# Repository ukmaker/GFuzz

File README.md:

# GFuzz
Guitar fuzz pedal with old-school fuzz-face and modern circuitry using germanium diodes

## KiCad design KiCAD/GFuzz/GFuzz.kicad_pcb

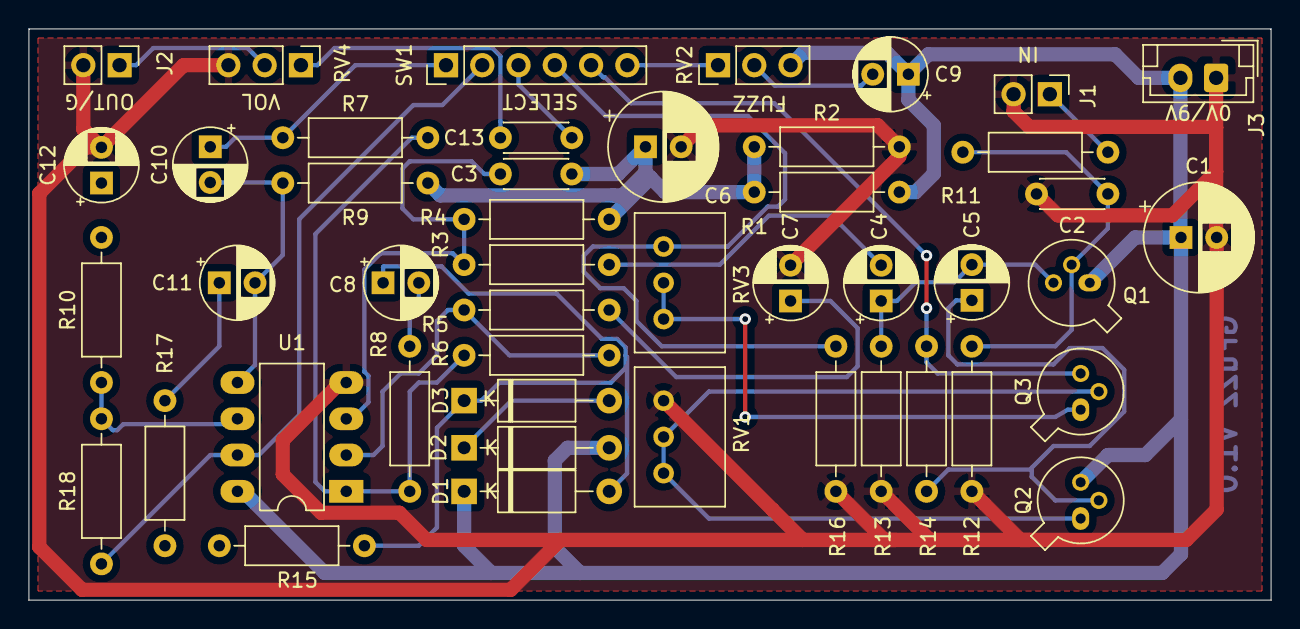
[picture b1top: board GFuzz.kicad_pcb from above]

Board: 2 copper layers, 87.0 x 40.0 mm, 46 parts (0 on the bottom side), 31 nets.

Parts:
C1, C6: 100u; CP_Radial_D7.5mm_P2.50mm
C2, C3: 1n; C_Disc_D4.3mm_W1.9mm_P5.00mm
C4, C5: 2u2; CP_Radial_D5.0mm_P2.50mm
C7, C8, C10, C11, C12: 10u; CP_Radial_D5.0mm_P2.50mm
C9: 20u; CP_Radial_D5.0mm_P2.50mm
C13: 100n; C_Disc_D4.3mm_W1.9mm_P5.00mm
D1, D2, D3: D; D_A-405_P10.16mm_Horizontal
J1, J2: Conn_Coaxial; PinHeader_1x02_P2.54mm_Vertical
J3: Conn_01x02; JST_EH_B2B-EH-A_1x02_P2.50mm_Vertical
Q1: Q_NJFET_DGS; TO-18-3
Q2, Q3: Q_PNP_CBE; TO-18-3
R1, R2, R3, R7, R9, R11: 10k; R_Axial_DIN0207_L6.3mm_D2.5mm_P10.16mm_Horizontal
R4, R12: 1M; R_Axial_DIN0207_L6.3mm_D2.5mm_P10.16mm_Horizontal
R5, R8, R13: 1k; R_Axial_DIN0207_L6.3mm_D2.5mm_P10.16mm_Horizontal
R6: 33k; R_Axial_DIN0207_L6.3mm_D2.5mm_P10.16mm_Horizontal
R10: 1K; R_Axial_DIN0207_L6.3mm_D2.5mm_P10.16mm_Horizontal
R14: 100k; R_Axial_DIN0207_L6.3mm_D2.5mm_P10.16mm_Horizontal
R15, R16, R17: 470; R_Axial_DIN0207_L6.3mm_D2.5mm_P10.16mm_Horizontal
R18: 2k2; R_Axial_DIN0207_L6.3mm_D2.5mm_P10.16mm_Horizontal
RV1, RV3: 100k; Potentiometer_Bourns_3299W_Vertical
RV2: 1k; PinHeader_1x03_P2.54mm_Vertical
RV4: 100k; PinHeader_1x03_P2.54mm_Vertical
SW1: SW_DPDT_x2_OddPinout; PinHeader_1x06_P2.54mm_Vertical
U1: TL072; DIP-8_W7.62mm_LongPads

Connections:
9V: C1.1, C9.1, D1.1, D2.2, J3.2, Q1.1, Q2.3, R1.2, RV2.3, U1.8
GND: C1.2, C2.2, C6.2, C7.2, C12.2, J1.2, J2.2, J3.1, R2.2, R12.2, R13.2, R16.1, RV1.1, RV4.3, U1.4
unnamed: C2.1, Q1.2, R11.1, R12.1
unnamed: C3.1, C6.1, R1.1, R2.1, R4.1, R9.2
unnamed: C3.2, R3.1, R4.2, U1.3
unnamed: C4.1, C5.2, Q1.3, R13.1
unnamed: C4.2, R3.2
unnamed: C5.1, Q2.2, R14.2
unnamed: C7.1, R5.2
unnamed: C8.1, D1.2, D3.1, R15.2
unnamed: C8.2, R8.1
unnamed: C9.2, RV2.2
unnamed: C10.1, R7.1, SW1.1
unnamed: C10.2, C11.2, R9.1, U1.5
unnamed: C11.1, R17.1
unnamed: C12.1, R10.2
unnamed: C13.1, RV4.1
unnamed: C13.2, SW1.3
unnamed: D2.1, D3.2
unnamed: J1.1, R11.2
unnamed: J2.1, RV4.2
unnamed: Q2.1, Q3.2, RV1.2, RV1.3
unnamed: Q3.1, RV3.2, RV3.3
unnamed: Q3.3, R14.1, SW1.5
unnamed: R5.1, R6.2, U1.2
unnamed: R6.1, R7.2, R8.2, U1.1
unnamed: R10.1, R18.2, U1.6
unnamed: R15.1, R17.2
unnamed: R16.2, RV3.1, SW1.4
unnamed: R18.1, SW1.2, U1.7
unnamed: RV2.1, SW1.6

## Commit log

2020-03-07 Initial import
2020-03-07 Removed RevC
